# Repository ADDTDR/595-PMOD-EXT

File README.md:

# 74HC595 Shift Register Output Extender

This project uses two serial shift registers (74HC595) and a 74HCT08 quad AND gate as a buffer to ensure stable input and output signal operation. The buffer prevents signal overload on input pins, even when multiple modules are daisy-chained.

Built module 

KiCad render 

### Inputs for the 74HC595 Shift Register:
- **SER**: Serial Data Input  
- **SRCLK**: Shift Register Clock  
- **RCLK**: Register Clock  

### Outputs:
- Two PMOD-compatible connectors  

This setup allows for efficient signal management and easy extension of digital outputs.

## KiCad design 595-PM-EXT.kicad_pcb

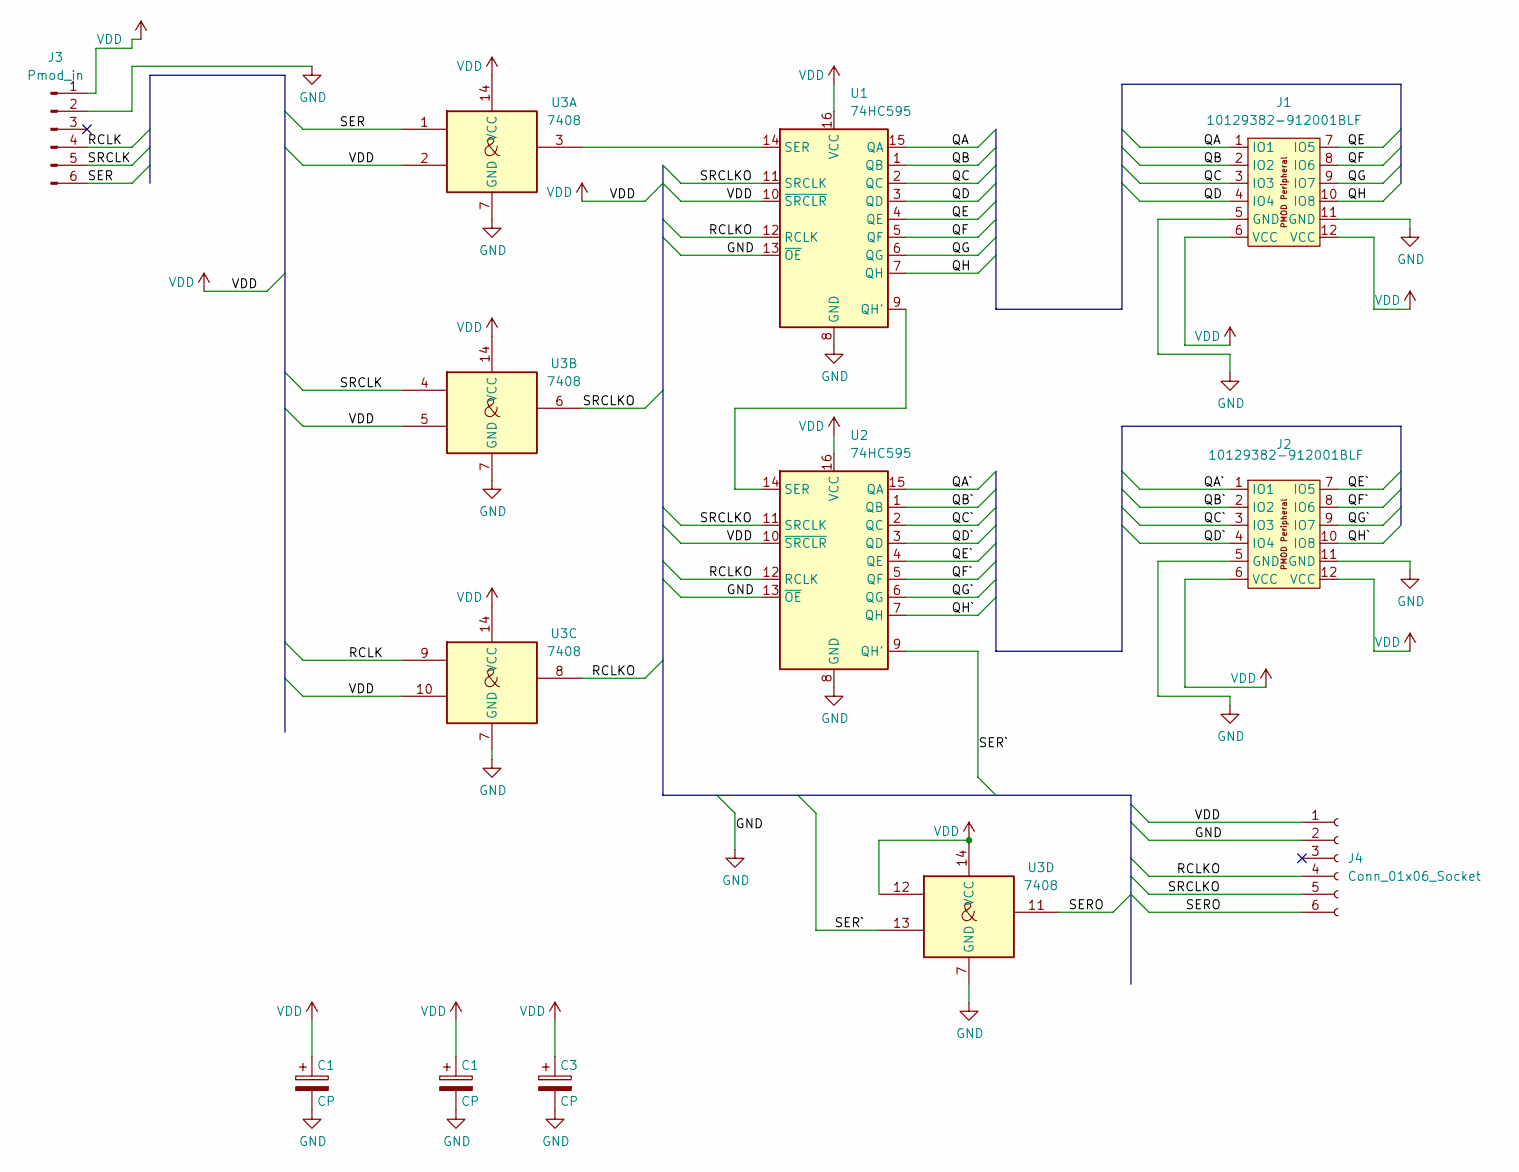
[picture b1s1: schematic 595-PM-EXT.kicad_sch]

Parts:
C1, C3: CP; C_Disc_D4.3mm_W1.9mm_P5.00mm
J1, J2: 10129382-912001BLF; pmod-f; LCSC Part C492434
J3: Pmod_in; PinHeader_1x06_P2.54mm_Horizontal
J4: Conn_01x06_Socket; PinSocket_1x06_P2.54mm_Horizontal
U1, U2: 74HC595; DIP-16_W7.62mm_LongPads
U3: 7408; DIP-14_W7.62mm

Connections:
/QA: J1.1 (IO1), U1.15 (QA)
/QA`: J2.1 (IO1), U2.15 (QA)
/QB: J1.2 (IO2), U1.1 (QB)
/QB`: J2.2 (IO2), U2.1 (QB)
/QC: J1.3 (IO3), U1.2 (QC)
/QC`: J2.3 (IO3), U2.2 (QC)
/QD: J1.4 (IO4), U1.3 (QD)
/QD`: J2.4 (IO4), U2.3 (QD)
/QE: J1.7 (IO5), U1.4 (QE)
/QE`: J2.7 (IO5), U2.4 (QE)
/QF: J1.8 (IO6), U1.5 (QF)
/QF`: J2.8 (IO6), U2.5 (QF)
/QG: J1.9 (IO7), U1.6 (QG)
/QG`: J2.9 (IO7), U2.6 (QG)
/QH: J1.10 (IO8), U1.7 (QH)
/QH`: J2.10 (IO8), U2.7 (QH)
/RCLK: J3.4, U3.9
/RCLKO: J4.4, U1.12 (RCLK), U2.12 (RCLK), U3.8
/SER: J3.6, U3.1
/SERO: J4.6, U3.11
/SER`: U2.9 (QH'), U3.13
/SRCLK: J3.5, U3.4
/SRCLKO: J4.5, U1.11 (SRCLK), U2.11 (SRCLK), U3.6
GND: C1.2, C3.2, J1.5 (GND), J1.11 (GND), J2.5 (GND), J2.11 (GND), J3.2, J4.2, U1.8 (GND), U1.13 (~OE), U2.8 (GND), U2.13 (~OE), U3.7 (GND); also elsewhere on the board
unnamed: U1.9 (QH'), U2.14 (SER)
unnamed: U1.14 (SER), U3.3
VDD: C1.1, C3.1, J1.6 (VCC), J1.12 (VCC), J2.6 (VCC), J2.12 (VCC), J3.1, J4.1, U1.10 (~SRCLR), U1.16 (VCC), U2.10 (~SRCLR), U2.16 (VCC), U3.2, U3.5, U3.10, U3.12, U3.14 (VCC); also elsewhere on the board

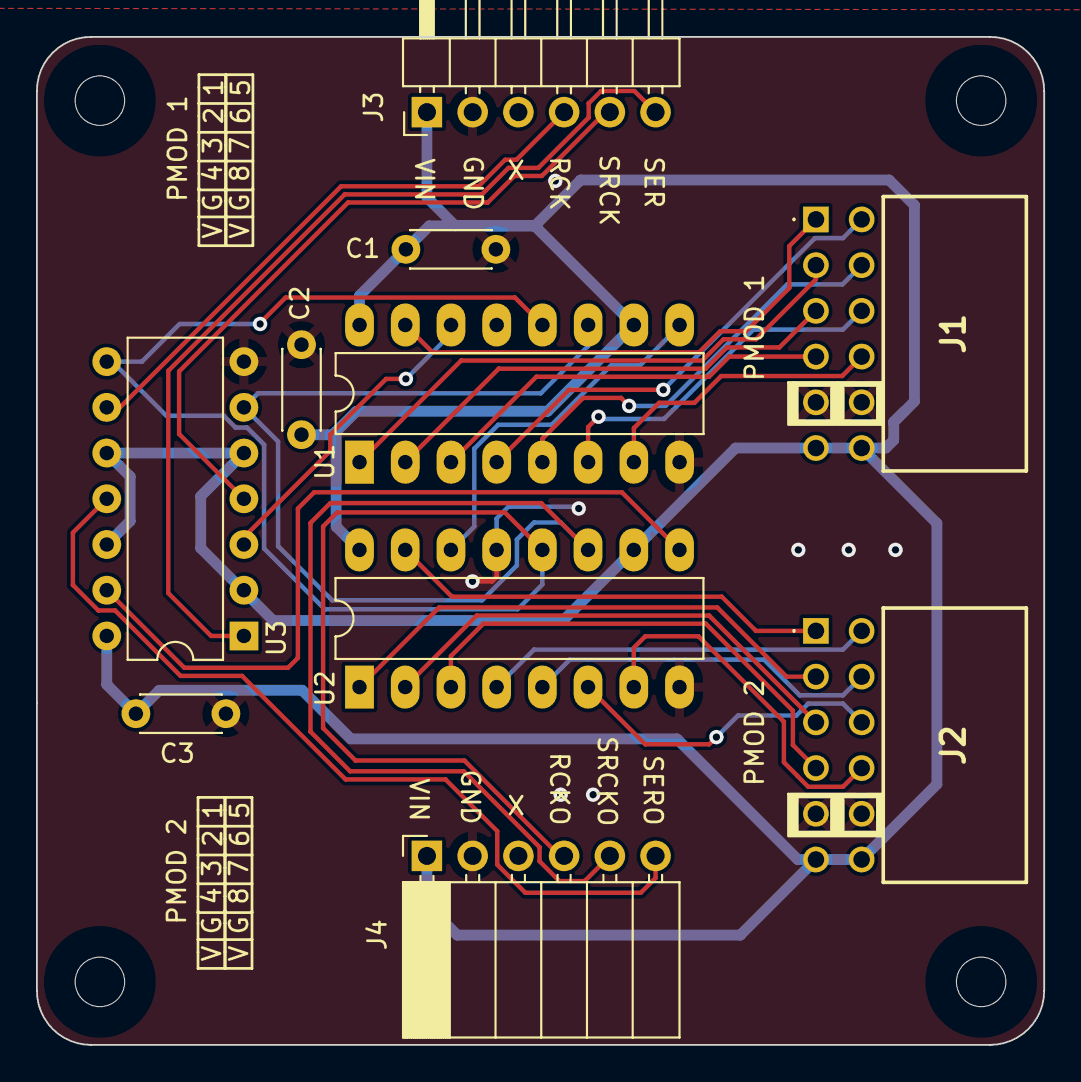
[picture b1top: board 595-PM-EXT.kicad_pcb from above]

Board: 2 copper layers, 56.0 x 56.0 mm, 10 parts (0 on the bottom side), 27 nets.

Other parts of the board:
C2: CP; C_Disc_D4.3mm_W1.9mm_P5.00mm

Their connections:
GND: C2.2; also elsewhere on the board
VDD: C2.1; also elsewhere on the board
